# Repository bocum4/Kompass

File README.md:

____   ____   _____ _    _ __  __          
 |  _ \ / __ \ / ____| |  | |  \/  |   /\    
 | |_) | |  | | |    | |  | | \  / |  /  \   
 |  _ <| |  | | |    | |  | | |\/| | / /\ \  
 | |_) | |__| | |____| |__| | |  | |/ ____ \ 
 |____/ \____/ \_____|\____/|_|  |_/_/    \_\

KOMPASS DIGITAL MINI SYTNH.

Related Project Files. 

Este proyecto está basado en el Nebulophone de Dr. Bleep (Nos quitamos el sombrero ante su ingenio). 

https://bleeplabs.com/product/nebulophone/

Se modificó el ruteo de los pines del ATMega para permitir la adición de un sensor capacitivo MPR121
como motor principal del teclado háptico y re-diseñamos la interfaz según nuestros intereses. Todos 
los archivos de programación y manufactura se hacen disponibles aquí bajo la misma licencia 
del proyecto original. 

Creative Commons Attribution-ShareAlike 3.0 Unported License 

Para mas info: contacto@bocuma.mx 

#somosbocuma

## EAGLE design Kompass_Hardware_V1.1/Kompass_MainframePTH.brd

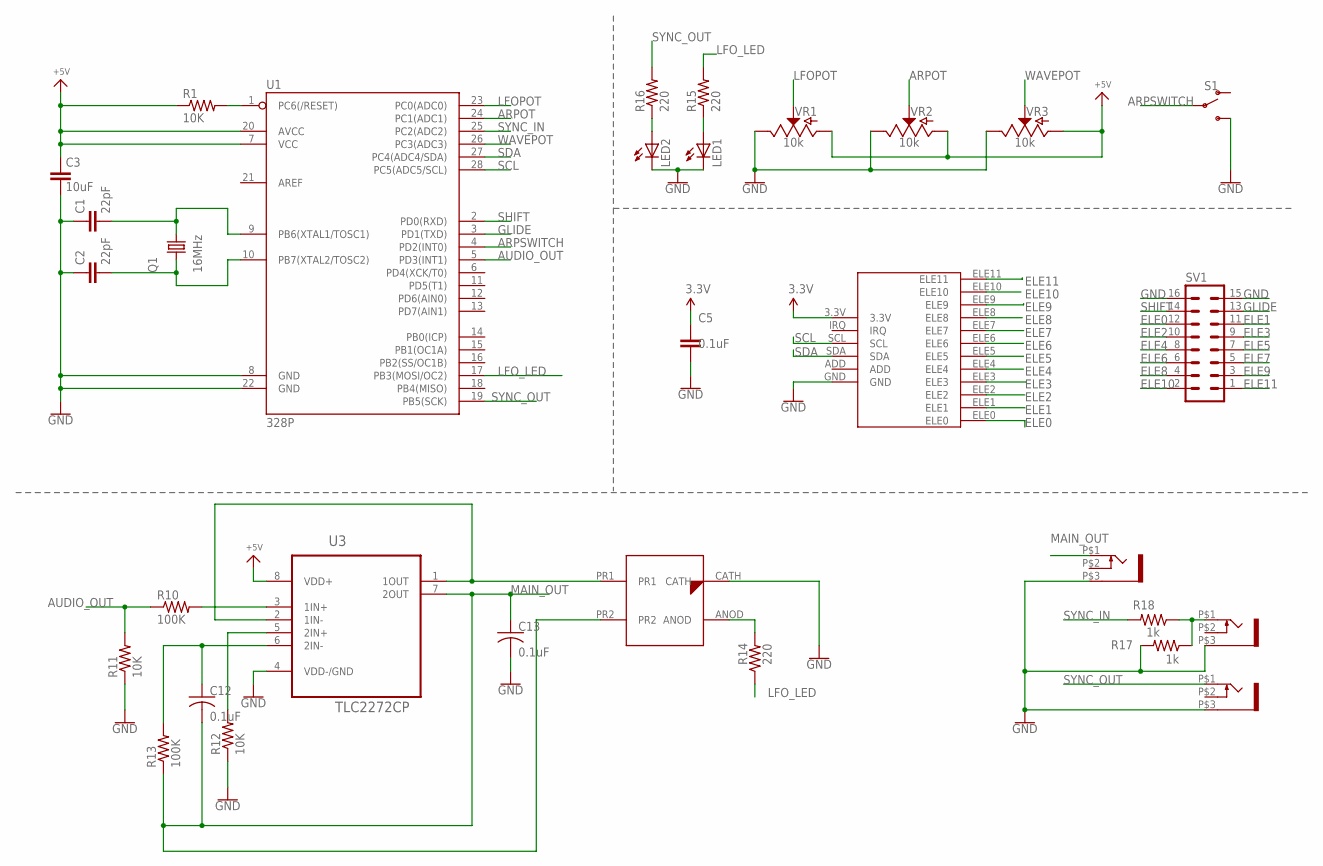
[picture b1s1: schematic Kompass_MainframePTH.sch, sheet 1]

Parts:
C1, C2: 22pF; C2.5-3
C3: 10uF; C025-025X050
C5: 0.1uF; C2.5-3
C12, C13: 0.1uF; C025-024X044
LED1, LED2: LED3MM
Q1: 16MHz; HC49/S
R1, R11, R12: 10K; 0204/5
R10, R13: 100K; 0204/5
R14, R15, R16: 220; 0204/5
R17, R18: 1k; 0204/5
S1: SWITCH-SPDT-PTH-11.6X4.0MM; SWITCH_SPDT_PTH_11.6X4.0MM
SV1: MA08-2
U1: 328P; DIP28
U3: TLC2272CP; DIP254P762X508-8
U$1: BOCUMA_VACTROLBMA_VACTROL_PTH; BOCUMA_VACTROL
U$2, U$3, U$4: WQP-PJ301M-12_JACK
U$6: MPR121_BREAKOUT
VR1, VR2, VR3: 10k; POT-PTH-ALPS

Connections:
3.3V: C5.1, U$6.3.3V; also elsewhere on the board
ARPOT: U1.24 (PC1(ADC1)), VR2.P$2 (S)
ARPSWITCH: S1.2, U1.4 (PD2(INT0))
AUDIO_OUT: R10.1, R11.2, U1.5 (PD3(INT1))
ELE0: SV1.12, U$6.ELE0
ELE1: SV1.11, U$6.ELE1
ELE2: SV1.10, U$6.ELE2
ELE3: SV1.9, U$6.ELE3
ELE4: SV1.8, U$6.ELE4
ELE5: SV1.7, U$6.ELE5
ELE6: SV1.6, U$6.ELE6
ELE7: SV1.5, U$6.ELE7
ELE8: SV1.4, U$6.ELE8
ELE9: SV1.3, U$6.ELE9
ELE10: SV1.2, U$6.ELE10
ELE11: SV1.1, U$6.ELE11
GLIDE: SV1.13, U1.3 (PD1(TXD))
GND: C1.1, C2.1, C3.2, C5.2, C13.2, LED1.K (C), LED2.K (C), R11.1, R12.1, R17.2, S1.3 (S), SV1.15, SV1.16, U1.8 (GND), U1.22 (GND), U3.4 (VDD-/GND), U$1.CATH, U$2.P$3 (1), U$3.P$3 (1), U$4.P$3 (1), U$6.GND, VR1.P$1 (E), VR2.P$1 (E), VR3.P$1 (E); also elsewhere on the board
LFOPOT: U1.23 (PC0(ADC0)), VR1.P$2 (S)
LFO_LED: R14.1, R15.2, U1.17 (PB3(MOSI/OC2))
MAIN_OUT: C12.2, C13.1, R13.1, U3.7 (2OUT), U$1.PR2, U$4.P$1 (2)
unnamed: C1.2, Q1.2, U1.9 (PB6(XTAL1/TOSC1))
unnamed: C2.2, Q1.1, U1.10 (PB7(XTAL2/TOSC2))
unnamed: R1.2, U1.1 (PC6(/RESET))
unnamed: C12.1, R13.2, U3.6 (2IN-)
unnamed: R12.2, U3.5 (2IN+)
unnamed: U3.1 (1OUT), U3.2 (1IN-), U$1.PR1
unnamed: R10.2, U3.3 (1IN+)
unnamed: R14.2, U$1.ANOD
unnamed: LED1.A, R15.1
unnamed: LED2.A, R16.1
unnamed: R17.1, R18.1, U$2.P$1 (2)
SCL: U1.28 (PC5(ADC5/SCL)), U$6.SCL
SDA: U1.27 (PC4(ADC4/SDA)), U$6.SDA
SHIFT: SV1.14, U1.2 (PD0(RXD))
SYNC_IN: R18.2, U1.25 (PC2(ADC2))
SYNC_OUT: R16.2, U1.19 (PB5(SCK)), U$3.P$1 (2)
VCC: C3.1, R1.1, U1.7 (VCC), U1.20 (AVCC), U3.8 (VDD+), VR1.P$3 (A), VR2.P$3 (A), VR3.P$3 (A); also elsewhere on the board
WAVEPOT: U1.26 (PC3(ADC3)), VR3.P$2 (S)

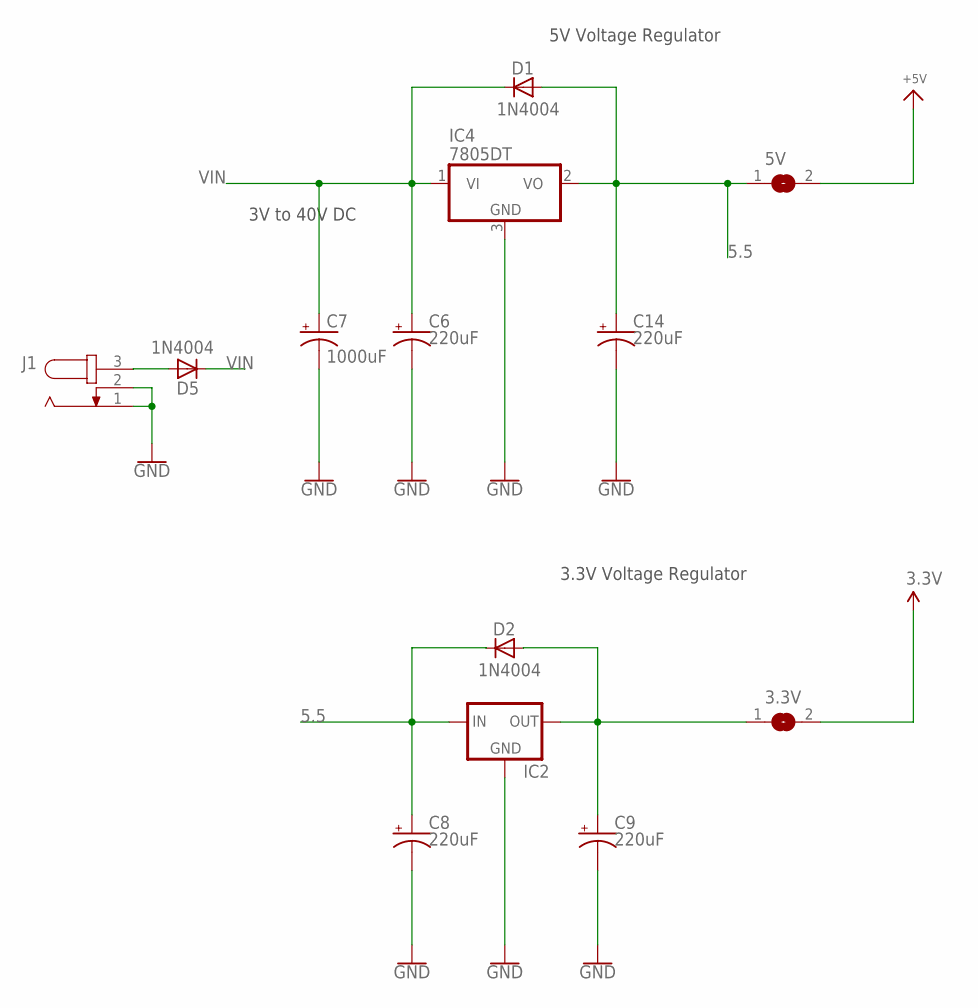
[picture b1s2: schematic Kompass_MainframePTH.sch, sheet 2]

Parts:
3.3V, 5V: SJW
C6, C8, C9, C14: 220uF; E2,5-6E
C7: 1000uF; E3,5-8
D1, D2, D5: 1N4004; DO41-10
IC2: 78LXX
IC4: 7805DT; TO252
J1: JACK-PLUG0; SPC4077

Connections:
3.3V: 3.3V.2; also elsewhere on the board
5.5: 5V.1, C8.+, C14.+, D1.A, D2.C, IC2.IN, IC4.2 (VO)
GND: C6.-, C7.-, C8.-, C9.-, C14.-, IC2.GND, IC4.3 (GND), J1.1, J1.2; also elsewhere on the board
unnamed: D5.A, J1.3
unnamed: 3.3V.1, C9.+, D2.A, IC2.OUT
VCC: 5V.2; also elsewhere on the board
VIN: C6.+, C7.+, D1.C, D5.C, IC4.1 (VI)

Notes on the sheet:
5V Voltage Regulator
3V to 40V DC
3.3V Voltage Regulator

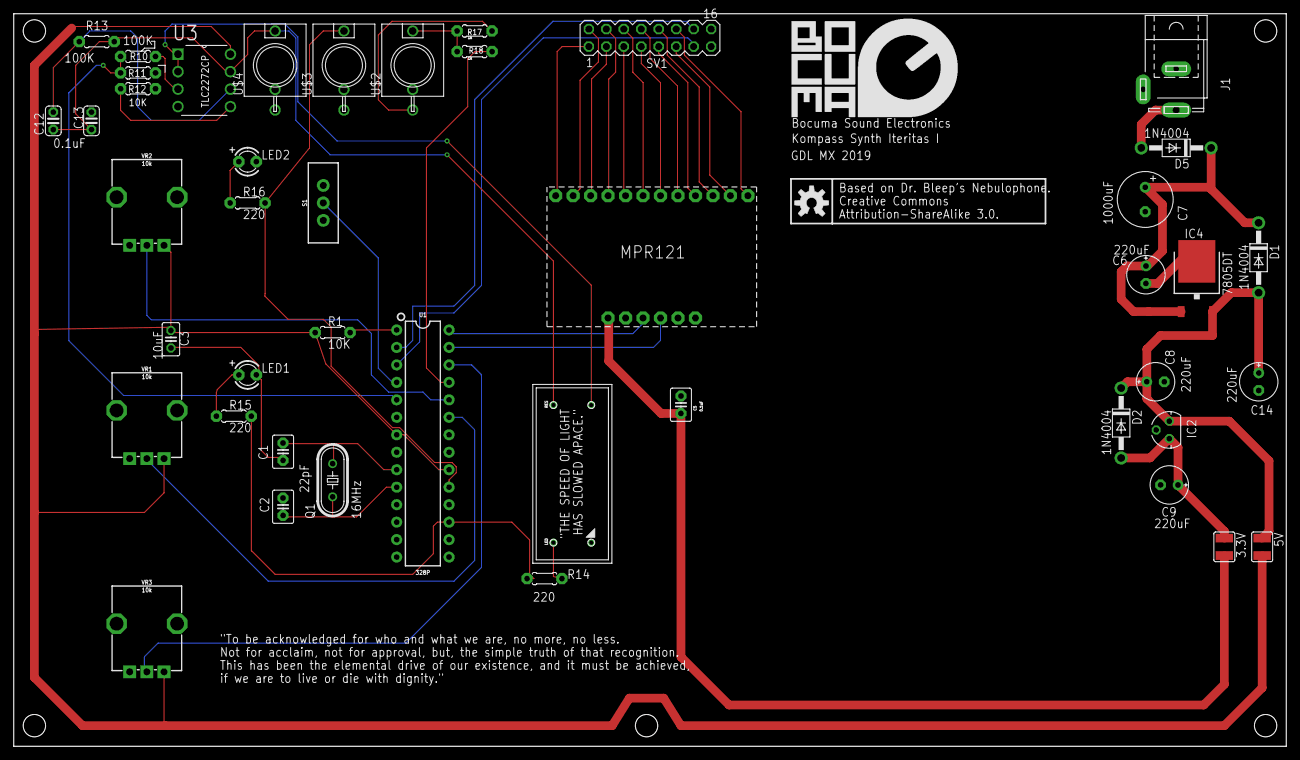
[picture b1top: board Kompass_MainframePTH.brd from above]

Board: 2 copper layers, 185.0 x 106.5 mm, 45 parts (0 on the bottom side), 43 nets.

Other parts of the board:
U$5: OSHW-LOGO-M

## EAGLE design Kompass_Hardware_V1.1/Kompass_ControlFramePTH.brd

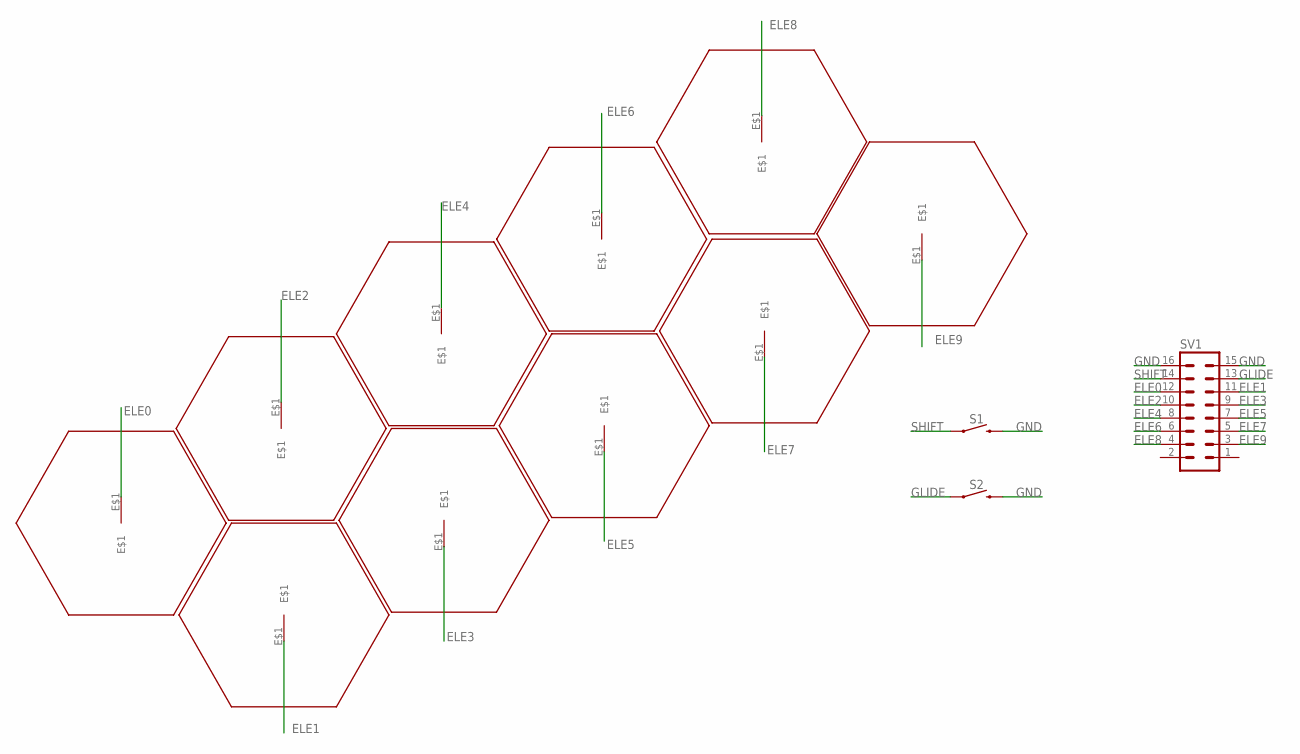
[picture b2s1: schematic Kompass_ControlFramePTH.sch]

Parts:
ELE0, ELE1, ELE2, ELE3, ELE4, ELE5, ELE6, ELE7, ELE8, ELE9: HEX_ELECTRODEHEX_ELECTRODEPAD; HEX_ELECTRODE
S1, S2: MOMENTARY-SWITCH-SPST-PTH-6.0MM-KIT; TACTILE_SWITCH_PTH_6.0MM_KIT
SV1: MA08-2

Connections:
ELE0: ELE0.E$1, SV1.12
ELE1: ELE1.E$1, SV1.11
ELE2: ELE2.E$1, SV1.10
ELE3: ELE3.E$1, SV1.9
ELE4: ELE4.E$1, SV1.8
ELE5: ELE5.E$1, SV1.7
ELE6: ELE6.E$1, SV1.6
ELE7: ELE7.E$1, SV1.5
ELE8: ELE8.E$1, SV1.4
ELE9: ELE9.E$1, SV1.3
GLIDE: S2.1, SV1.13
GND: S1.3 (2), S2.3 (2), SV1.15, SV1.16
SHIFT: S1.1, SV1.14

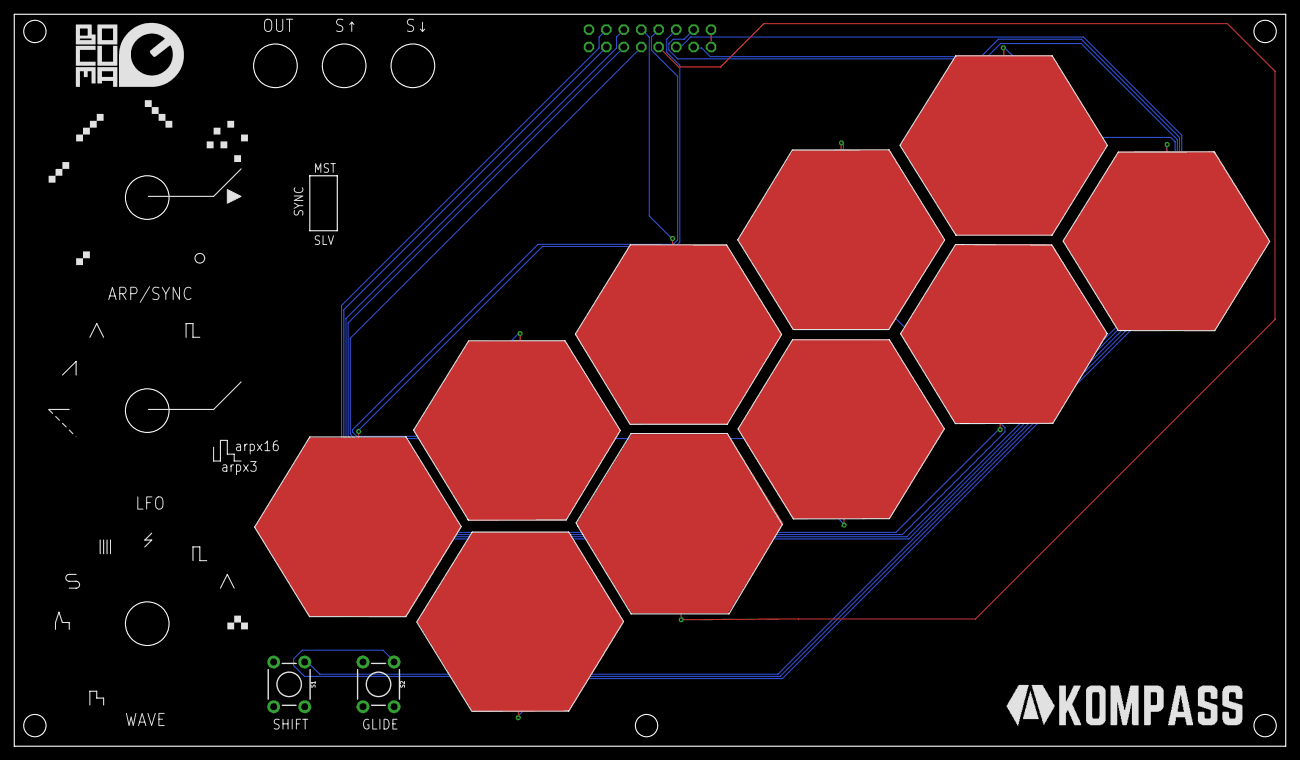
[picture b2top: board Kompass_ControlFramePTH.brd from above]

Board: 2 copper layers, 185.0 x 106.5 mm, 13 parts (0 on the bottom side), 13 nets.

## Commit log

2020-09-06 Add files via upload
    Add Kompass User Guide in .pdf format
2020-09-13 Upload project files
    Uploaded manufacturing and programming files. Updated readme.md

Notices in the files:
parts and their libraries:
SparkFun-Switches: Licensing: Creative Commons ShareAlike 4.0 International - https://creativecommons.org/licenses/by-sa/4.0
